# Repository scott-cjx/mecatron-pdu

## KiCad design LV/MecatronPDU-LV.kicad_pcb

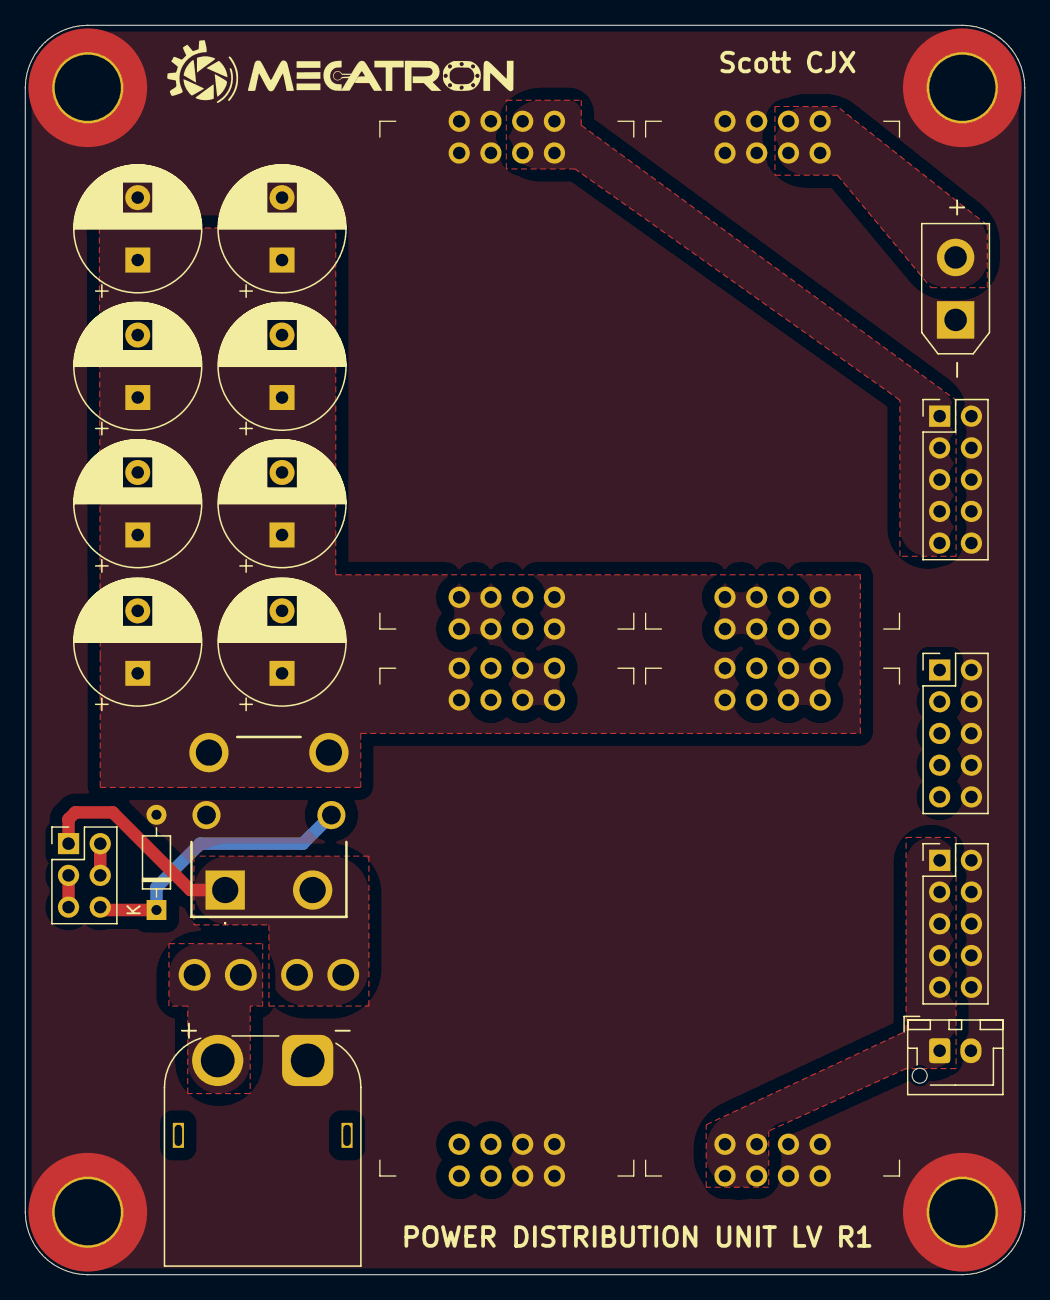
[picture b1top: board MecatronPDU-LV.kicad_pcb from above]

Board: 2 copper layers, 80.0 x 100.0 mm, 26 parts (0 on the bottom side), 11 nets.

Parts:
C101, C102, C103, C104, C105, C106, C107, C108: 560u; CP_Radial_D10.0mm_P5.00mm
D101: D; D_DO-35_SOD27_P7.62mm_Horizontal
F101: Fuse; FUSE-MCCQ-122
H101, H102, H103, H104: MountingHole_Pad_MP; MountingHole_5.3mm_M5_ISO7380_Pad_TopBottom
J101: Power In; AMASS_XT60PW-M_1x02_P7.20mm_Horizontal
J102: E-Stops; PinHeader_2x03_P2.54mm_Vertical
J201: V_{HV}; JST_XH_B2B-XH-AM_1x02_P2.50mm_Vertical
J202, J203, J204: V; PinHeader_2x05_P2.54mm_Vertical
J205: V_{SBC}; AMASS_XT30UPB-M_1x02_P5.0mm_Vertical
K101: Relay_SPST-NO; G8PM1AW7RDC12
U201, U202, U203, U204: TPS5460 康威科技

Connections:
+5V: J202.1, J202.3, J202.5, J202.7, J202.9, U202.2 (V_{OUT})
+9V: J203.1, J203.3, J203.5, J203.7, J203.9, U203.2 (V_{OUT})
+12V: J201.1, J204.1, J204.3, J204.5, J204.7, J204.9, U204.2 (V_{OUT})
/VCC_FUSE: F101.2, J102.1, K101.14
GND: C101.2, C102.2, C103.2, C104.2, C105.2, C106.2, C107.2, C108.2, D101.2 (A), H101.1, H102.1, H103.1, H104.1, J101.1, J201.2, J202.2, J202.4, J202.6, J202.8, J202.10, J203.2, J203.4, J203.6, J203.8, J203.10, J204.2, J204.4, J204.6, J204.8, J204.10, J205.1, K101.A2, U201.G (GND), U202.G (GND), U203.G (GND), U204.G (GND)
unnamed: D101.1 (K), J102.6, K101.A1
unnamed: J102.2, J102.4
unnamed: J102.3, J102.5
VCC: F101.1, J101.2
VCCF: C101.1, C102.1, C103.1, C104.1, C105.1, C106.1, C107.1, C108.1, K101.13, U201.1 (V_{IN}), U202.1 (V_{IN}), U203.1 (V_{IN}), U204.1 (V_{IN})
V_{SBC}: J205.2, U201.2 (V_{OUT})

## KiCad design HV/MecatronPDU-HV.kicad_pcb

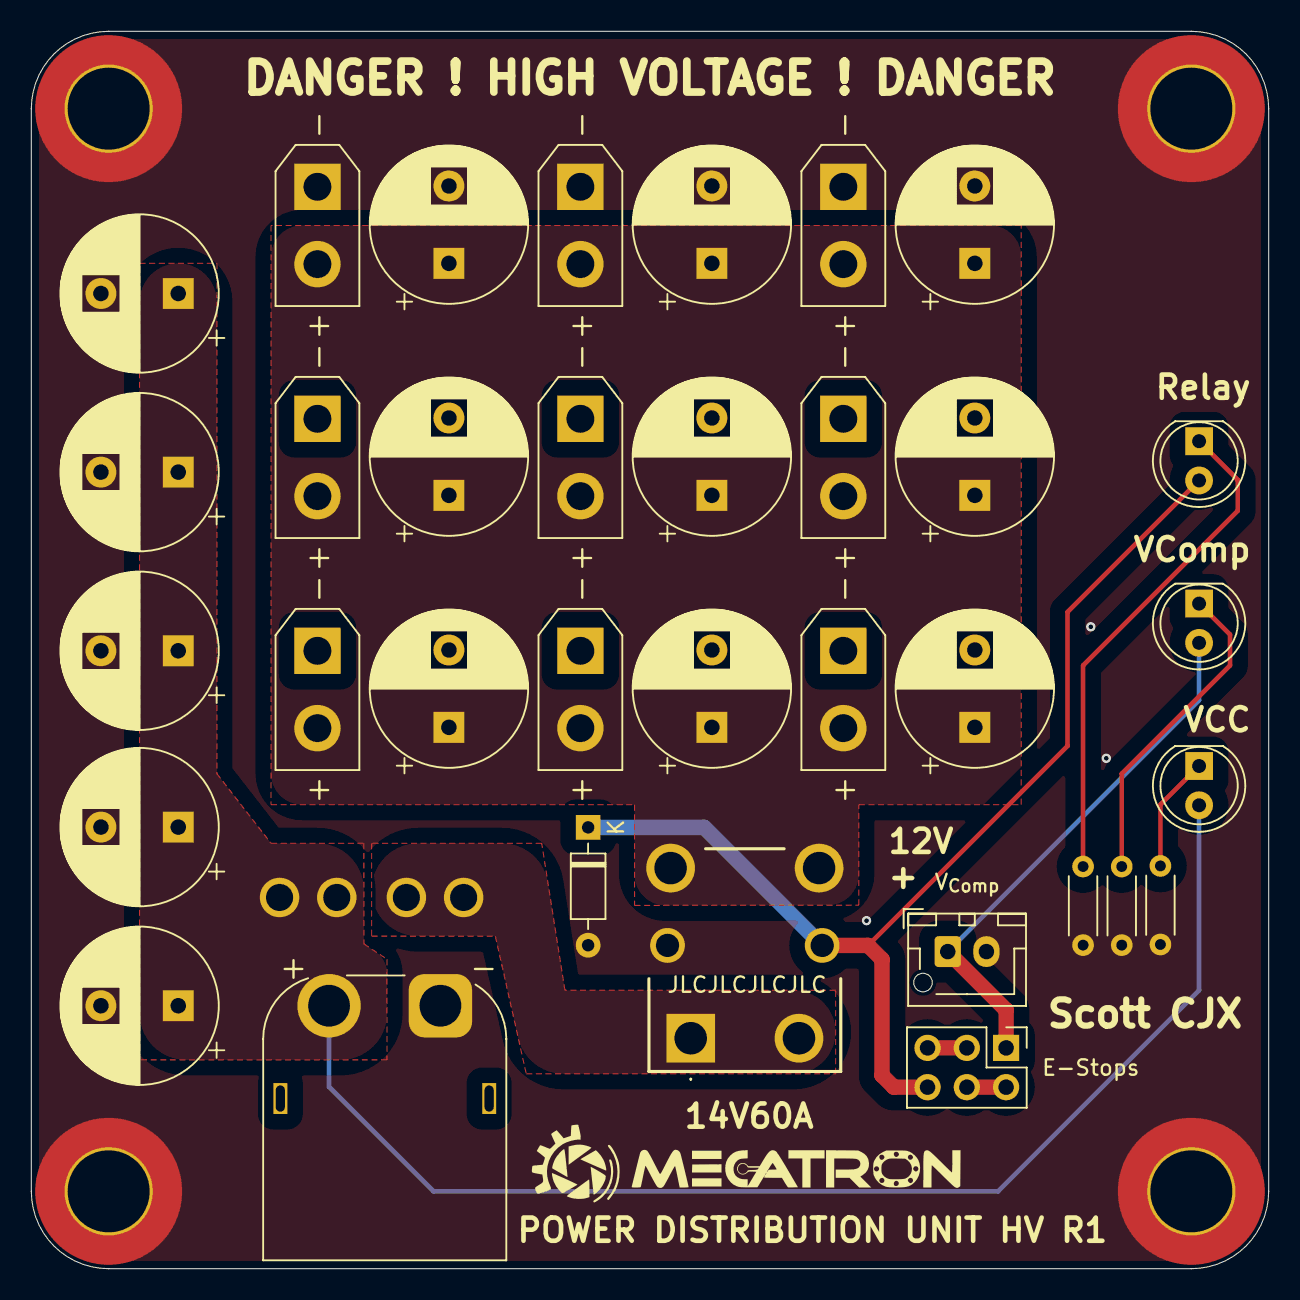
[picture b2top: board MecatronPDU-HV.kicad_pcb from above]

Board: 2 copper layers, 80.0 x 80.0 mm, 39 parts (0 on the bottom side), 11 nets.

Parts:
C101, C102, C103, C104, C105, C201, C202, C203, C204, C205, C206, C207, C208, C209: 560u; CP_Radial_D10.0mm_P5.00mm
D101: 1N4148; D_DO-35_SOD27_P7.62mm_Horizontal
D102, D103, D104: LED; LED_D5.0mm_Clear
F101: Fuse; FUSE-MCCQ-122
H101, H102, H103, H104: MountingHole_Pad_MP; MountingHole_5.3mm_M5_ISO7380_Pad_TopBottom
J101: Power In; AMASS_XT60PW-M_1x02_P7.20mm_Horizontal
J102: V_{Comp}; JST_XH_B2B-XH-AM_1x02_P2.50mm_Vertical
J106: E-Stops; PinHeader_2x03_P2.54mm_Vertical
J201, J202, J203, J204, J205, J206, J207, J208, J209: Power Out; AMASS_XT30UPB-F_1x02_P5.0mm_Vertical
K101: Relay_SPST-NO; G8PM1AW7RDC12
R101, R102, R103: 1k; R_Axial_DIN0204_L3.6mm_D1.6mm_P5.08mm_Horizontal

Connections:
/VCC_FUSE: F101.2, K101.14
/relay_sig: D101.1 (K), D104.2 (A), J106.6, K101.A1
GND: C101.2, C102.2, C103.2, C104.2, C105.2, C201.2, C202.2, C203.2, C204.2, C205.2, C206.2, C207.2, C208.2, C209.2, D101.2 (A), H101.1, H102.1, H103.1, H104.1, J101.1, J102.2, J201.1, J202.1, J203.1, J204.1, J205.1, J206.1, J207.1, J208.1, J209.1, K101.A2, R101.2, R102.2, R103.2
unnamed: D102.1 (K), R101.1
unnamed: D103.1 (K), R103.1
unnamed: D104.1 (K), R102.1
unnamed: J106.2, J106.4
unnamed: J106.3, J106.5
VCC: C101.1, C102.1, C103.1, C104.1, C105.1, D102.2 (A), F101.1, J101.2
VCCF: C201.1, C202.1, C203.1, C204.1, C205.1, C206.1, C207.1, C208.1, C209.1, J201.2, J202.2, J203.2, J204.2, J205.2, J206.2, J207.2, J208.2, J209.2, K101.13
V_{Comp}: D103.2 (A), J102.1, J106.1

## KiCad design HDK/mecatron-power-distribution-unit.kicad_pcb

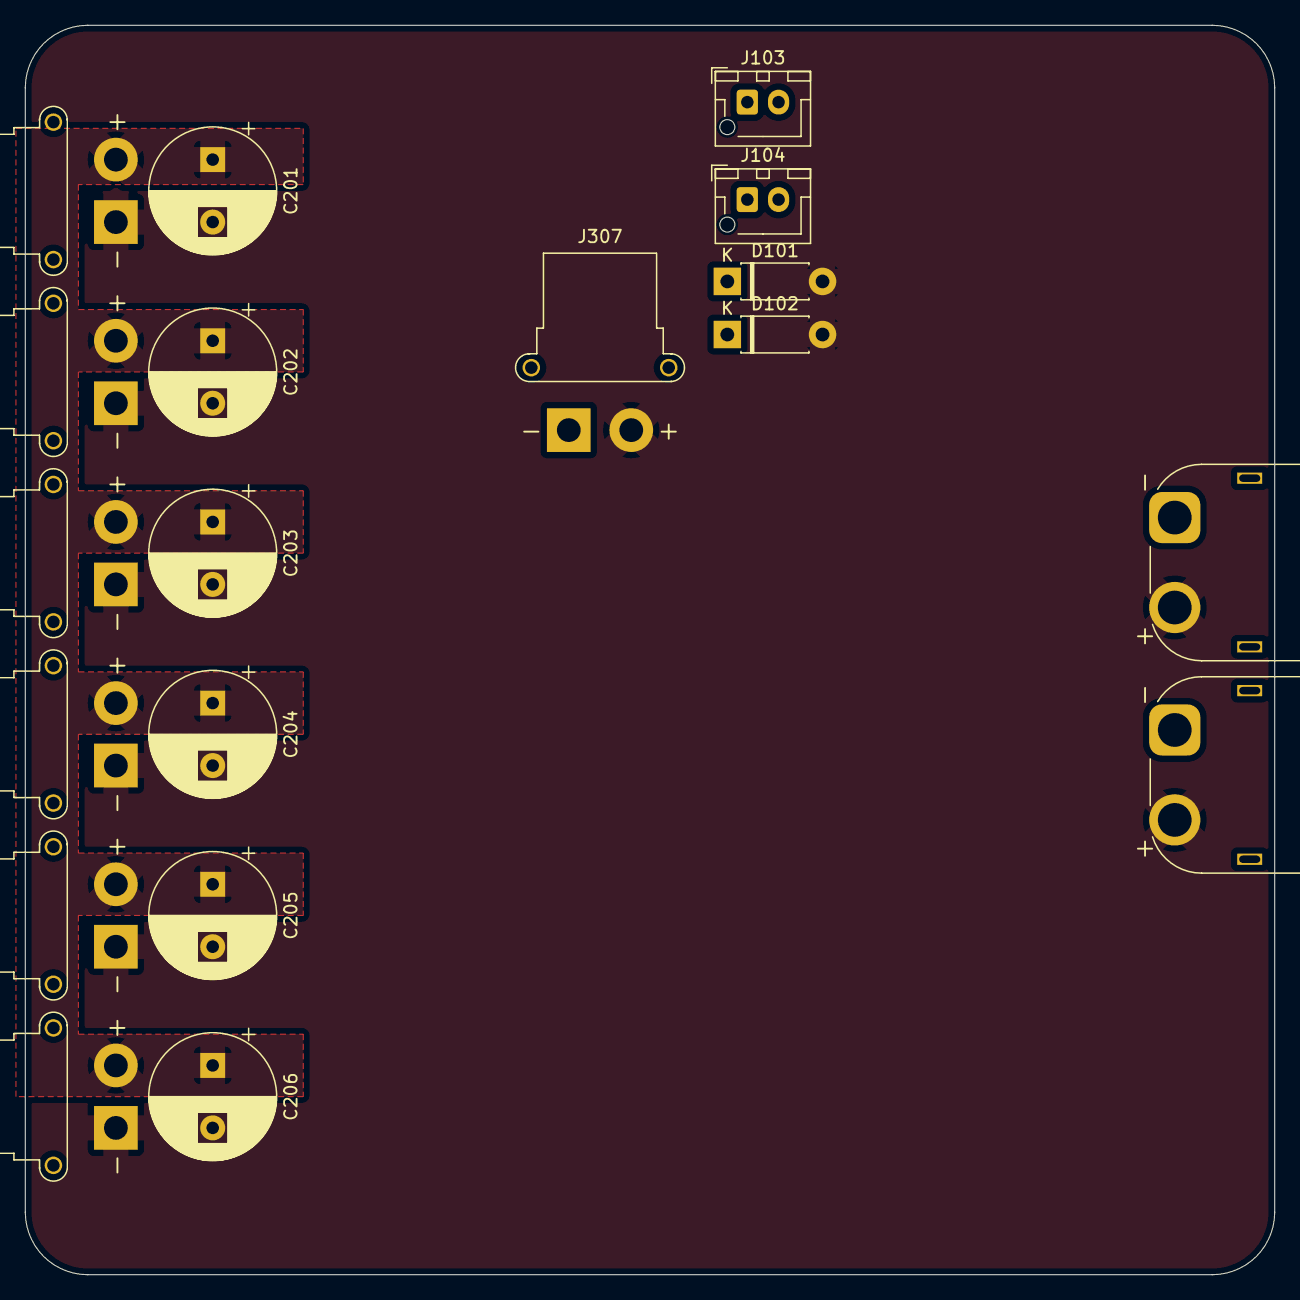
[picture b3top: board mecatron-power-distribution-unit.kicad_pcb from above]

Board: 2 copper layers, 100.0 x 100.0 mm, 19 parts (0 on the bottom side), 4 nets, no tracks yet.

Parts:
C201, C202, C203, C204, C205, C206: 560u; CP_Radial_D10.0mm_P5.00mm
D101, D102: 1N4004; D_DO-41_SOD81_P7.62mm_Horizontal
J101: PwrIn_{1}; AMASS_XT60PW-M_1x02_P7.20mm_Horizontal
J102: PwrIn_{2}; AMASS_XT60PW-M_1x02_P7.20mm_Horizontal
J103: E-Stop; JST_XH_B2B-XH-AM_1x02_P2.50mm_Vertical
J104: PwrSw; JST_XH_B2B-XH-AM_1x02_P2.50mm_Vertical
J201, J202, J203, J204, J205, J206: P1-Out; AMASS_XT30PW-F_1x02_P2.50mm_Horizontal
J307: PwrOut_{2}; AMASS_XT30PW-F_1x02_P2.50mm_Horizontal

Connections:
GND: C201.2, C202.2, C203.2, C204.2, C205.2, C206.2, D101.2 (A), D102.2 (A), J101.2, J102.2, J201.1, J202.1, J203.1, J204.1, J205.1, J206.1, J307.2
unnamed: D101.1 (K), J103.2
unnamed: D102.1 (K), J104.2
VCCF_{Sec}: C201.1, C202.1, C203.1, C204.1, C205.1, C206.1, J201.2, J202.2, J203.2, J204.2, J205.2, J206.2

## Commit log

2024-07-17 init commit
2024-07-18 added working v1
2024-07-18 updated docs
2024-07-18 Deployed b2135c7 with MkDocs version: 1.6.0
2024-08-21 updated sch
2024-08-28 added connectors
2024-09-02 updated split of stack
2024-09-15 added HV
2024-09-16 final HV
2024-09-16 added lv
2024-09-16 Deployed 6675678 with MkDocs version: 1.6.1
